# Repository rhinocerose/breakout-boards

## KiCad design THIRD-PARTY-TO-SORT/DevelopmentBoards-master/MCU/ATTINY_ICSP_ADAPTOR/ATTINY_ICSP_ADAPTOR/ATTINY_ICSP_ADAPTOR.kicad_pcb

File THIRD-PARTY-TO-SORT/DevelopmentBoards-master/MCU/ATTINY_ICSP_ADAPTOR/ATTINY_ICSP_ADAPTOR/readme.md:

<h2> ATTiny85 breadboard adaptor </h2>

<h3>Schematic</h3>

<h3>3D Renders</h3>

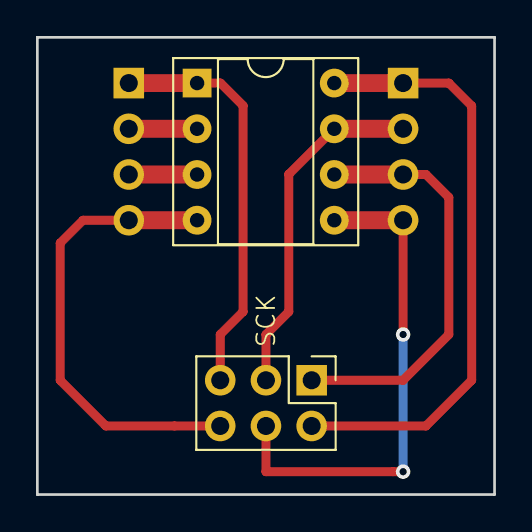
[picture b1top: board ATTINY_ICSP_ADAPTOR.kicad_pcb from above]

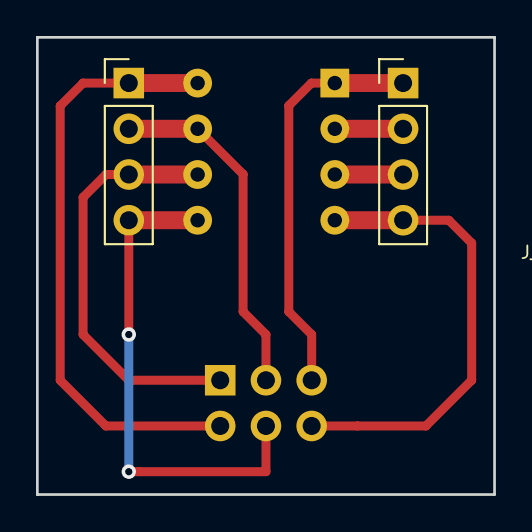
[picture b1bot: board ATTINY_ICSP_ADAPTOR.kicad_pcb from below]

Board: 2 copper layers, 25.4 x 25.4 mm, 4 parts (2 on the bottom side), 8 nets.

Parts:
J_ICSP1: AVR-ISP-6; PinHeader_2x03_P2.54mm_Vertical
J_PINS_1-4, J_PINS_5-8: Conn_01x04; PinHeader_1x04_P2.54mm_Vertical
U_MCU1: ATtiny85-20PU; DIP-8_W7.62mm_Socket

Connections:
unnamed: J_ICSP1.1, J_PINS_5-8.3, U_MCU1.6
unnamed: J_ICSP1.2, J_PINS_5-8.1, U_MCU1.8
unnamed: J_ICSP1.3, J_PINS_5-8.2, U_MCU1.7
unnamed: J_ICSP1.4, J_PINS_5-8.4, U_MCU1.5
unnamed: J_ICSP1.5, J_PINS_1-4.1, U_MCU1.1
unnamed: J_ICSP1.6, J_PINS_1-4.4, U_MCU1.4
unnamed: J_PINS_1-4.2, U_MCU1.2
unnamed: J_PINS_1-4.3, U_MCU1.3

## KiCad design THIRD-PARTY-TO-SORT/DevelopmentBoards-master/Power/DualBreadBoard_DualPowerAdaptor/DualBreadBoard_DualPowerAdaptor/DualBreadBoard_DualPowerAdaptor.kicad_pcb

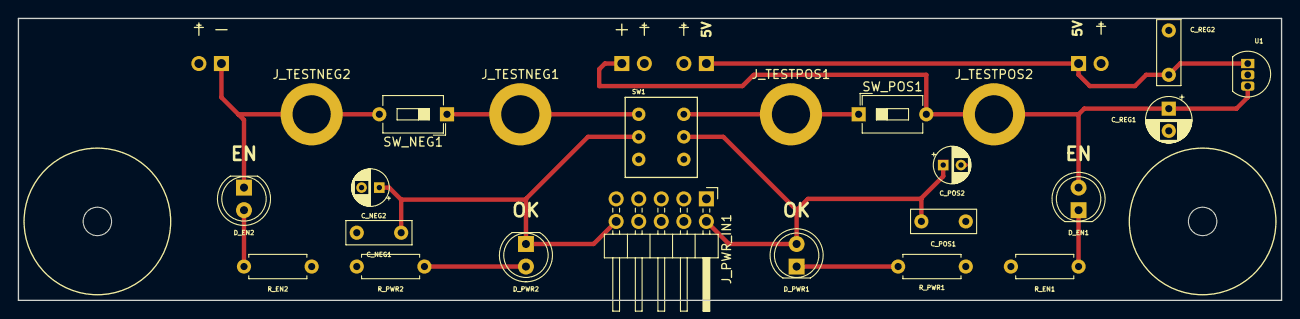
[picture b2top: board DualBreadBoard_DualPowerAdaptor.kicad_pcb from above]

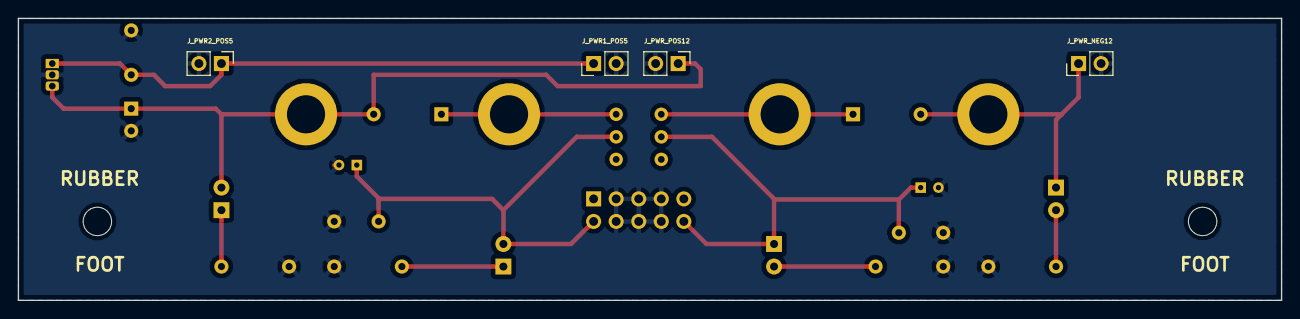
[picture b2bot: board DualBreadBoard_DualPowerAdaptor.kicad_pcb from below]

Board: 2 copper layers, 142.2 x 31.8 mm, 27 parts (4 on the bottom side), 12 nets.

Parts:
C_NEG1: 100nF; C_Rect_L7.2mm_W2.5mm_P5.00mm_FKS2_FKP2_MKS2_MKP2
C_NEG2: 10uF; CP_Radial_D4.0mm_P2.00mm
C_POS1: 100nF; C_Rect_L7.2mm_W2.5mm_P5.00mm_FKS2_FKP2_MKS2_MKP2
C_POS2: 10uF; CP_Radial_D4.0mm_P2.00mm
C_REG1: 330nF; CP_Radial_D5.0mm_P2.50mm
C_REG2: 100nF; C_Rect_L7.2mm_W2.5mm_P5.00mm_FKS2_FKP2_MKS2_MKP2
D_EN1, D_EN2: RED; LED_D5.0mm
D_PWR1, D_PWR2: RED; LED_D5.0mm
J_PWR1_POS5, J_PWR2_POS5: Conn_01x02; PinHeader_1x02_P2.54mm_Vertical
J_PWR_IN1: Conn_02x05_Odd_Even; PinHeader_2x05_P2.54mm_Horizontal
J_PWR_NEG12: Conn_01x02; PinHeader_1x02_P2.54mm_Vertical
J_PWR_POS12: Conn_01x02; PinHeader_1x02_P2.54mm_Vertical
J_TESTNEG1, J_TESTNEG2: Conn_01x01; MountingHole_4.3mm_M4_ISO14580_Pad
J_TESTPOS1, J_TESTPOS2: Conn_01x01; MountingHole_4.3mm_M4_ISO14580_Pad
R_EN1, R_EN2: 1K; R_Axial_DIN0207_L6.3mm_D2.5mm_P7.62mm_Horizontal
R_PWR1, R_PWR2: 1K; R_Axial_DIN0207_L6.3mm_D2.5mm_P7.62mm_Horizontal
SW1: SW_DPDT_x2; DPST_ToggleONOFF
SW_NEG1: SW_SPST; SW_DIP_SPSTx01_Slide_6.7x4.1mm_W7.62mm_P2.54mm_LowProfile
SW_POS1: SW_SPST; SW_DIP_SPSTx01_Slide_6.7x4.1mm_W7.62mm_P2.54mm_LowProfile
U1: LM78L05_TO92; TO-92L_Inline

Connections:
/5V: C_REG2.1, J_PWR1_POS5.1, J_PWR2_POS5.1, U1.1
/+12V: C_REG1.1, D_EN1.2, J_PWR_POS12.1, J_TESTPOS2.1, SW_POS1.2, U1.3
/-12V: D_EN2.1, J_PWR_NEG12.1, J_TESTNEG2.1, SW_NEG1.2
/GND: C_NEG1.1, C_NEG2.2, C_POS1.2, C_POS2.2, C_REG1.2, C_REG2.2, J_PWR1_POS5.2, J_PWR2_POS5.2, J_PWR_IN1.3, J_PWR_IN1.4, J_PWR_IN1.5, J_PWR_IN1.6, J_PWR_IN1.7, J_PWR_IN1.8, J_PWR_NEG12.2, J_PWR_POS12.2, R_EN1.1, R_EN2.1, R_PWR1.1, R_PWR2.1, U1.2
unnamed: C_NEG1.2, C_NEG2.1, D_PWR2.1, J_PWR_IN1.10, SW1.5
unnamed: C_POS1.1, C_POS2.1, D_PWR1.2, J_PWR_IN1.2, SW1.2
unnamed: D_EN1.1, R_EN1.2
unnamed: D_EN2.2, R_EN2.2
unnamed: D_PWR1.1, R_PWR1.2
unnamed: D_PWR2.2, R_PWR2.2
unnamed: J_TESTNEG1.1, SW1.4, SW_NEG1.1
unnamed: J_TESTPOS1.1, SW1.1, SW_POS1.1

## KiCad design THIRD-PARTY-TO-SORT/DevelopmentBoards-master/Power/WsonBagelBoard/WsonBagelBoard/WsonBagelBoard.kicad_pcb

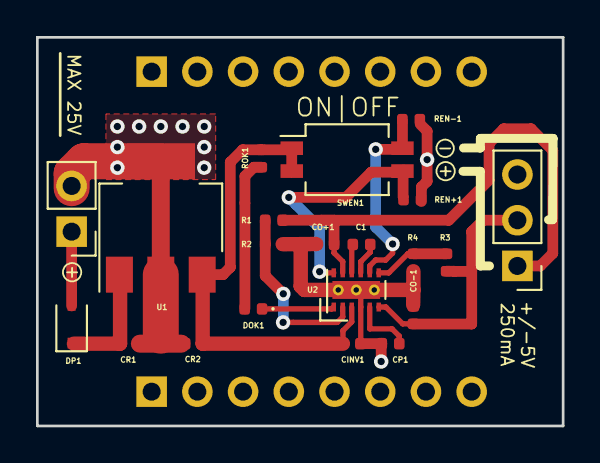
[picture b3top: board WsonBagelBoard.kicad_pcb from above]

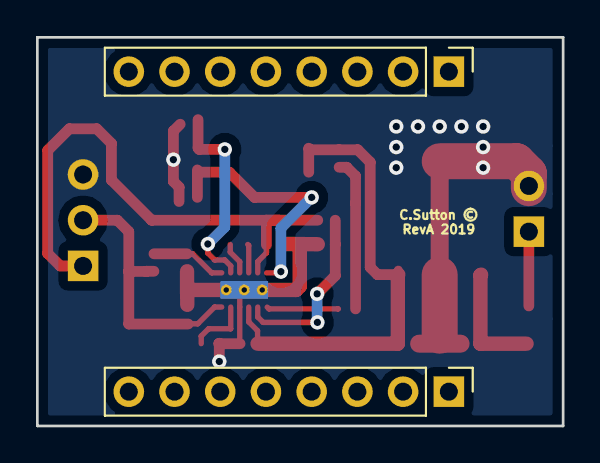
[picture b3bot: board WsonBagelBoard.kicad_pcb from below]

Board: 2 copper layers, 29.2 x 21.6 mm, 23 parts (2 on the bottom side), 15 nets.

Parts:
C1: 1u; C_0402_1005Metric
CINV1: 1u; C_0402_1005Metric
CO+1: 2.2u; C_0402_1005Metric
CO-1: 2.2u; C_0402_1005Metric
CP1: 4.7u; C_0402_1005Metric
CR1: C; C_0402_1005Metric
CR2: 100n; C_0402_1005Metric
DOK1: LED; LED_0402_1005Metric
DP1: D_Schottky; D_SOD-323
J_IN2: Conn_01x02; PinHeader_1x02_P2.54mm_Vertical
J_MNT1, J_MNT2: Conn_01x08; PinHeader_1x08_P2.54mm_Vertical
J_OUT1: Conn_01x03; PinHeader_1x03_P2.54mm_Vertical
R1, R3: 150K; R_0402_1005Metric
R2, R4: 50K; R_0402_1005Metric
REN+1: 10K; R_0402_1005Metric
REN-1: 10K; R_0402_1005Metric
ROK1: 10K; R_0402_1005Metric
SWEN1: SW_DIP_x02; SW_DIP_SPSTx02_Slide_Omron_A6H-2101_W6.15mm_P1.27mm
U1: uA7805; SOT-223-3_TabPin2
U2: LM27762; WSON-12-1EP_3x2mm_P0.5mm_EP1x2.65_ThermalVias

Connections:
/5VREG: CINV1.1, CR2.1, ROK1.2, SWEN1.1, SWEN1.2, U1.3, U2.3
/9VIN: CR1.1, DP1.1, U1.1
/EN+: REN+1.1, SWEN1.3, U2.12
/EN-: REN-1.1, SWEN1.4, U2.8
/GND: CINV1.2, CO+1.2, CO-1.2, CP1.2, CR1.2, CR2.2, J_IN2.2, J_OUT1.3, R2.1, R4.1, REN+1.2, REN-1.2, U1.2, U2.4, U2.13
/OUTREG+: CO+1.1, J_OUT1.1, R1.2, U2.11
/OUTREG-: CO-1.1, J_OUT1.2, R3.2, U2.6
/PGOOD: DOK1.1, U2.1
unnamed: C1.1, U2.9
unnamed: C1.2, U2.10
unnamed: CP1.1, U2.5
unnamed: DOK1.2, ROK1.1
unnamed: DP1.2, J_IN2.1
unnamed: R1.1, R2.2, U2.2
unnamed: R3.1, R4.2, U2.7

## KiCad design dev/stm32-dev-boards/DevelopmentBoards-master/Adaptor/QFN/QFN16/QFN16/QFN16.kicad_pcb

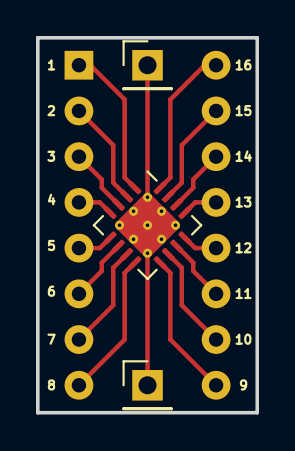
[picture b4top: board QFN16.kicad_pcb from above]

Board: 2 copper layers, 12.2 x 20.8 mm, 4 parts (0 on the bottom side), 17 nets.

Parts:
J_DIP16: Conn_01x16; DIP-16_W7.62mm_Socket
J_EP1, J_EP2: Conn_01x01; PinHeader_1x01_P2.54mm_Vertical
J_QFN16: Conn_01x17; QFN-16-1EP_4x4mm_P0.65mm_EP2.7x2.7mm_ThermalVias

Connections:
unnamed: J_DIP16.1, J_QFN16.1
unnamed: J_DIP16.2, J_QFN16.2
unnamed: J_DIP16.3, J_QFN16.3
unnamed: J_DIP16.4, J_QFN16.4
unnamed: J_DIP16.5, J_QFN16.5
unnamed: J_DIP16.6, J_QFN16.6
unnamed: J_DIP16.7, J_QFN16.7
unnamed: J_DIP16.8, J_QFN16.8
unnamed: J_DIP16.9, J_QFN16.9
unnamed: J_DIP16.10, J_QFN16.10
unnamed: J_DIP16.11, J_QFN16.11
unnamed: J_DIP16.12, J_QFN16.12
unnamed: J_DIP16.13, J_QFN16.13
unnamed: J_DIP16.14, J_QFN16.14
unnamed: J_DIP16.15, J_QFN16.15
unnamed: J_DIP16.16, J_QFN16.16
unnamed: J_EP1.1, J_EP2.1, J_QFN16.17

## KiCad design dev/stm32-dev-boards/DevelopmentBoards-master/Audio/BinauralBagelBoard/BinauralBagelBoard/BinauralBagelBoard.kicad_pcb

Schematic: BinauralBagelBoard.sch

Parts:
JIO1: Conn_02x02_Odd_Even; PinSocket_2x02_P2.54mm_Vertical
JMNT1, JMNT2: Conn_01x06; PinHeader_1x06_P2.54mm_Vertical
JOA1, JOA2: Conn_02x03_Odd_Even; PinSocket_2x03_P2.54mm_Vertical
JP_OA1, JP_OA2: Jumper; SolderJumper-2_P1.3mm_Open_TrianglePad1.0x1.5mm
J_INOUT1: JACK__MONO_2P_NC; JackSocket_Mono_PCB
J_PWRTHRU1, J_PWRTHRU2: Conn_01x03; PinHeader_1x03_P2.54mm_Horizontal
U_OA1: TL072; SOIC-8_3.9x4.9mm_P1.27mm

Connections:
/+5V: J_PWRTHRU1.3, J_PWRTHRU2.3, U_OA1.8 (V+)
/-5V: J_PWRTHRU1.2, J_PWRTHRU2.2, U_OA1.4 (V-)
/GND: JIO1.2, JIO1.4, J_INOUT1.2, J_INOUT1.3, J_INOUT1.4, J_PWRTHRU1.1, J_PWRTHRU2.1
/INOUT: JIO1.1, JIO1.3, J_INOUT1.1
/OAMA: JOA1.3, JOA1.4, JP_OA1.1, U_OA1.2 (-)
/OAMB: JOA2.3, JOA2.4, JP_OA2.1, U_OA1.6 (-)
/OAOA: JOA1.5, JOA1.6, JP_OA1.2, U_OA1.1
/OAOB: JOA2.5, JOA2.6, JP_OA2.2, U_OA1.7
/OAPA: JOA1.1, JOA1.2, U_OA1.3 (+)
/OAPB: JOA2.1, JOA2.2, U_OA1.5 (+)

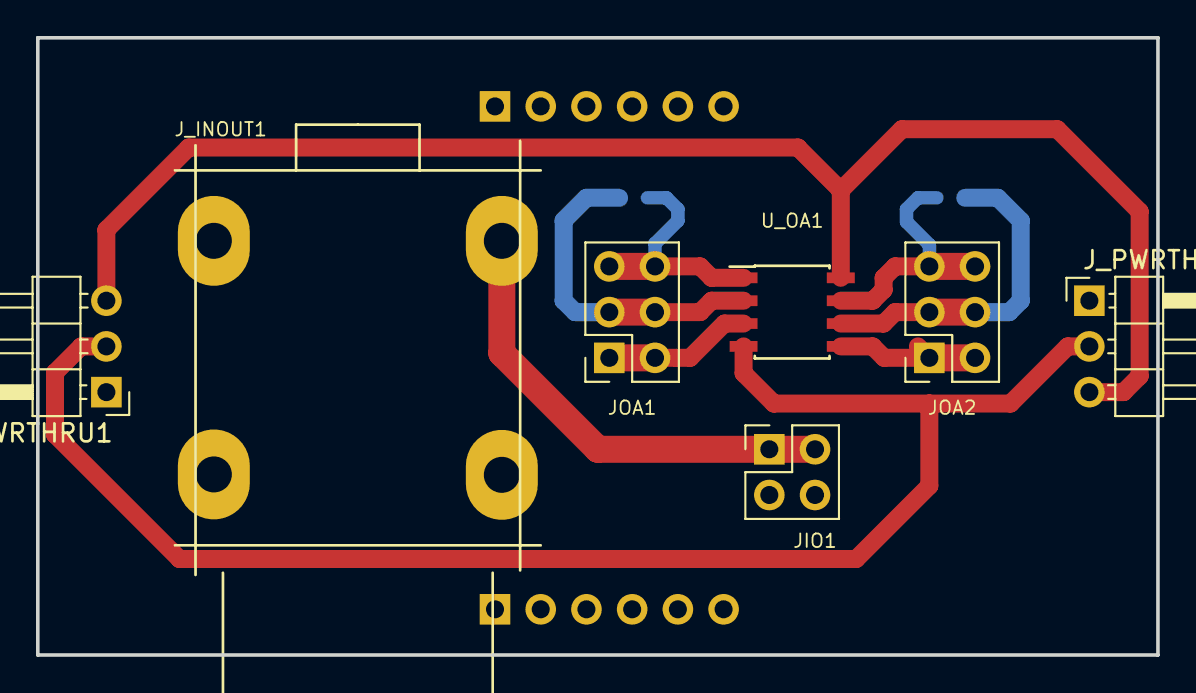
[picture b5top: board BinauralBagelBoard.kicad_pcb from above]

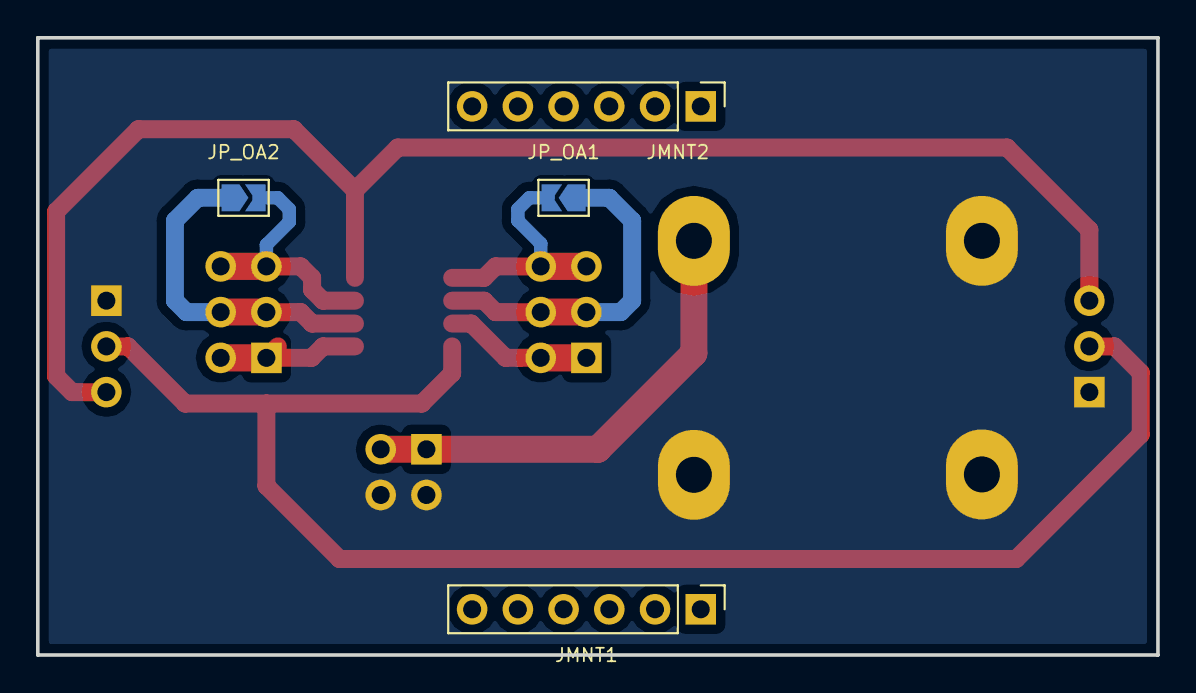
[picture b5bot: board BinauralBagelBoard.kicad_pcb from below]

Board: 2 copper layers, 62.2 x 34.3 mm, 11 parts (4 on the bottom side), 10 nets.

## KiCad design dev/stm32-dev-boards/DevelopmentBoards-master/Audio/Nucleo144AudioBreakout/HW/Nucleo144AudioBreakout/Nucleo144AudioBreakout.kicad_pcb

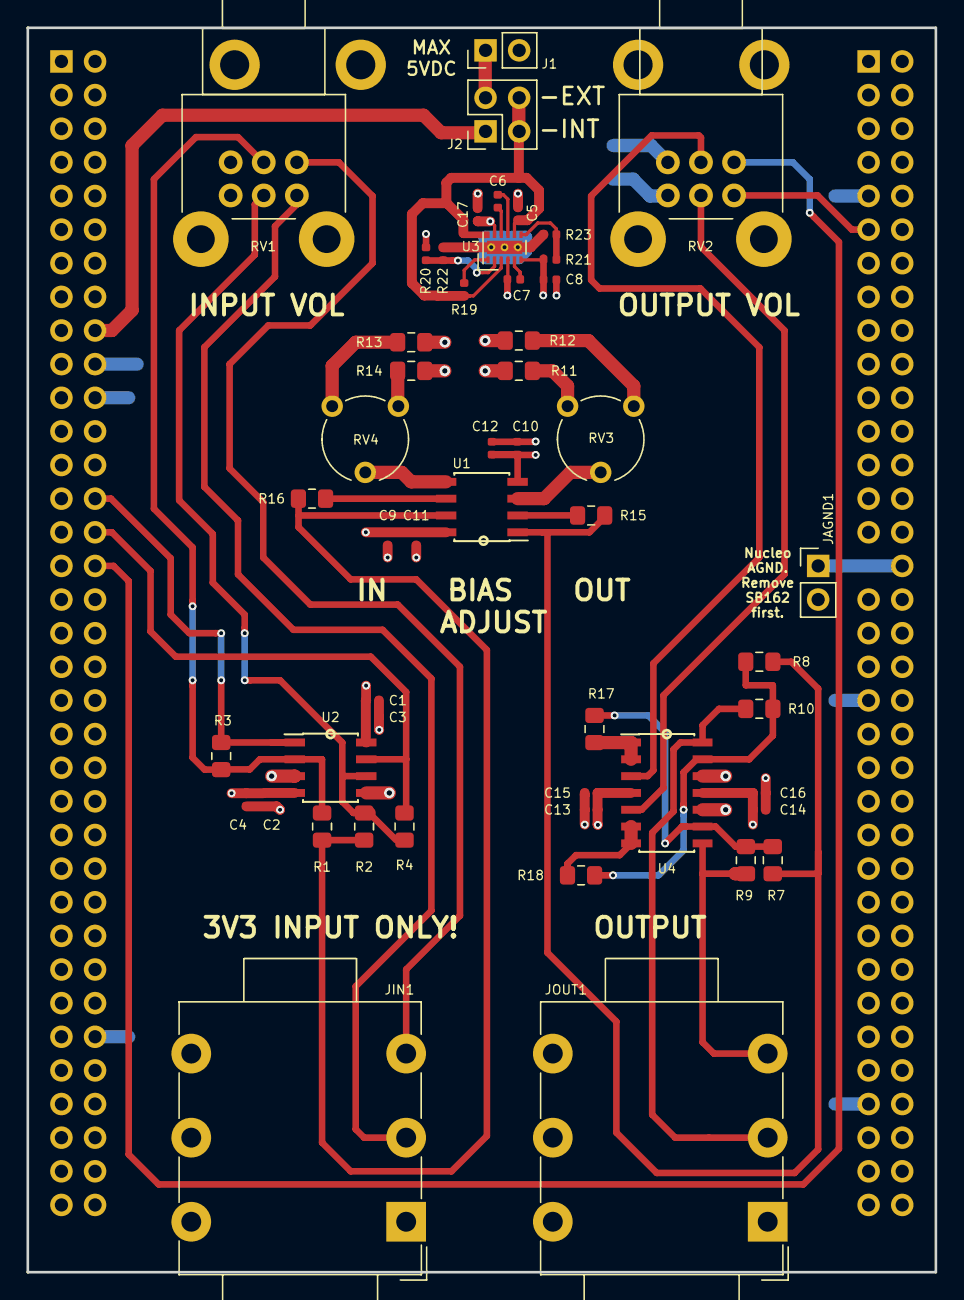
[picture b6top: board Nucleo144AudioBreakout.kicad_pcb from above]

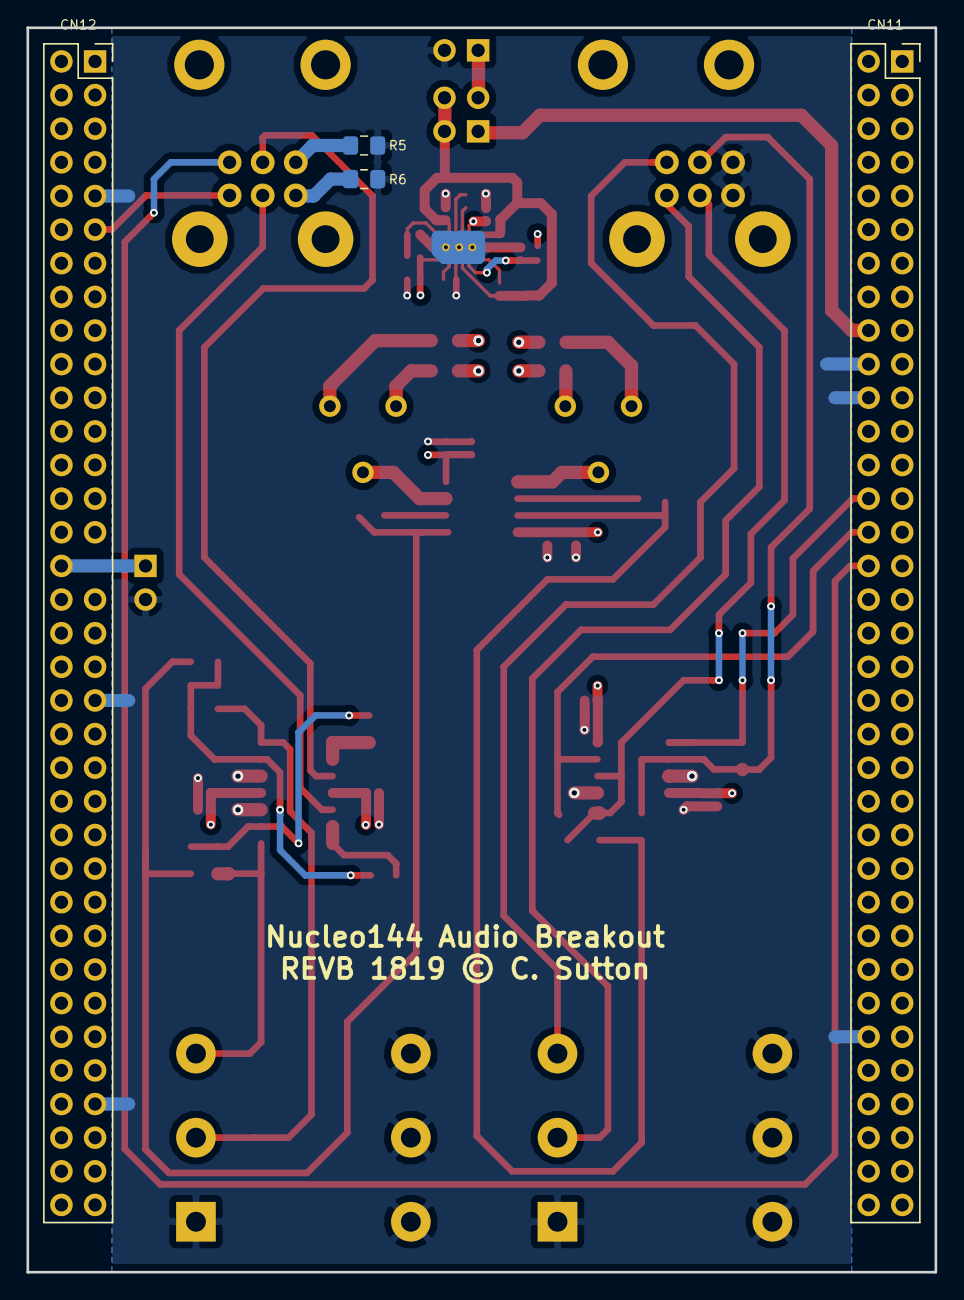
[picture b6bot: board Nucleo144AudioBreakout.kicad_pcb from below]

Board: 4 copper layers, 68.6 x 94.0 mm, 55 parts (4 on the bottom side), 41 nets.

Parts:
C1, C2, C9, C10, C13, C14: 100n; C_0402_1005Metric
C3, C4, C11, C12, C15, C16: 1u; C_0402_1005Metric
C5, C8, C17: 2.2u; C_0402_1005Metric
C6: 470n; C_0402_1005Metric
C7: 4.7u; C_0402_1005Metric
CN11, CN12: Nucleo144_Morpho; PinSocket_2x35_P2.54mm_Vertical
J1: Ext. Power; PinHeader_1x02_P2.54mm_Vertical
J2: Power Select; PinHeader_2x02_P2.54mm_Vertical
JAGND1: Conn_01x02; PinHeader_1x02_P2.54mm_Vertical
JIN1: Neutrik_NMJ6HFD2_TRS; Jack_3.5mm_Neutric_NMJ6HCD2_Horizontal
JOUT1: Neutrik_NMJ6HFD2_TRS; Jack_3.5mm_Neutric_NMJ6HCD2_Horizontal
R1, R2, R3, R4, R7, R8, R9, R10, R11, R12, R13, R14, R15, R16: 1K; R_0805_2012Metric_Pad1.15x1.40mm_HandSolder
R5, R6: 0R; R_0805_2012Metric_Pad1.15x1.40mm_HandSolder
R17, R18: 1k; R_0805_2012Metric_Pad1.15x1.40mm_HandSolder
R19: 10K; R_0402_1005Metric
R20, R21: 150K; R_0402_1005Metric
R22, R23: 50K; R_0402_1005Metric
RV1: 10K; Potentiometer_Alps_RK09L_Double_Horizontal
RV2: 100K; Potentiometer_Alps_RK09L_Double_Horizontal
RV3, RV4: 100K; Potentiometer_Piher_PT-6-V_Vertical
U1, U2: TL072; SOIC-8_3.9x4.9mm_P1.27mm
U3: LM27762; WSON-12-1EP_3x2mm_P0.5mm_EP1x2.65_ThermalVias
U4: TL074; SOIC-14_3.9x8.7mm_P1.27mm

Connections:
+5V: C1.1, C3.1, C9.1, C11.1, C13.1, C15.1, C17.1, R11.1, R13.1, R20.2, U1.8, U2.8, U3.11, U4.4
-5V: C2.1, C4.1, C8.1, C10.1, C12.1, C14.1, C16.1, R12.2, R14.2, R21.1, U1.4, U2.4, U3.6, U4.11
/FLAT_LINE_ADJUST_IN: R1.2, R2.2, R16.1, U1.7
/FLAT_LINE_ADJUST_OUT: R7.2, R8.2, R15.1, U1.1
/LM27762PSU/5V: C5.1, J2.3, J2.4, R19.2, U3.3, U3.8, U3.12
/LM27762PSU/VDDEXT: J1.1, J2.2
/PA0_ADC1_IN1: CN11.28, R3.1, U2.1
/PA1_ADC1_IN2: CN11.30, R4.1, U2.7
/PA4_DAC_OUT1: CN11.32, RV2.1
/PA5_DAC_OUT2: CN12.11, RV2.4
GNDS: C1.2, C2.2, C3.2, C4.2, C5.2, C7.1, C8.2, C9.2, C10.2, C11.2, C12.2, C13.2, C14.2, C15.2, C16.2, C17.2, CN11.20, CN11.22, CN11.60, CN12.9, CN12.39, CN12.63, J1.2, JAGND1.2, JIN1.1, JIN1.4, JIN1.5, JIN1.6, JOUT1.1, JOUT1.4, JOUT1.5, JOUT1.6, R5.1, R6.1, R22.1, R23.2, RV1.3, RV1.6, U2.3, U2.5, U3.4, U3.13, U4.10, U4.12
unnamed: C6.1, U3.9
unnamed: C6.2, U3.10
unnamed: C7.2, U3.5
unnamed: CN12.32, JAGND1.1
unnamed: JIN1.2, RV1.1
unnamed: JIN1.3, RV1.4
unnamed: JOUT1.2, R9.1, U4.8
unnamed: JOUT1.3, R10.1, U4.14
unnamed: R1.1, R3.2, RV1.2, U2.2
unnamed: R2.1, R4.2, RV1.5, U2.6
unnamed: R5.2, RV2.3
unnamed: R6.2, RV2.6
unnamed: R8.1, R10.2, R18.2, U4.13
unnamed: R11.2, RV3.1
unnamed: R12.1, RV3.3
unnamed: R13.2, RV4.1
unnamed: R14.1, RV4.3
unnamed: R15.2, U1.2
unnamed: R16.2, U1.6
unnamed: R17.1, U4.1, U4.2
unnamed: R7.1, R9.2, R17.2, U4.9
unnamed: R18.1, U4.6, U4.7
unnamed: R19.1, U3.1
unnamed: R20.1, R22.2, U3.2
unnamed: R21.2, R23.1, U3.7
unnamed: RV2.2, U4.3
unnamed: RV2.5, U4.5
unnamed: RV3.2, U1.3
unnamed: RV4.2, U1.5
VDD: CN11.18, J2.1

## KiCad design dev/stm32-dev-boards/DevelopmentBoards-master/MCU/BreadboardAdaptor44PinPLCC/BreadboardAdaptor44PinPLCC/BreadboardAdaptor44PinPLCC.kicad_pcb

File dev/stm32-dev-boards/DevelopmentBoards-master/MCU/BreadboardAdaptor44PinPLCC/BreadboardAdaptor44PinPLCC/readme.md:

<h2> 44Pin PLCC breadboard adaptor </h2>

<h3>Schematic</h3>

<h3> Board Layout</h3>

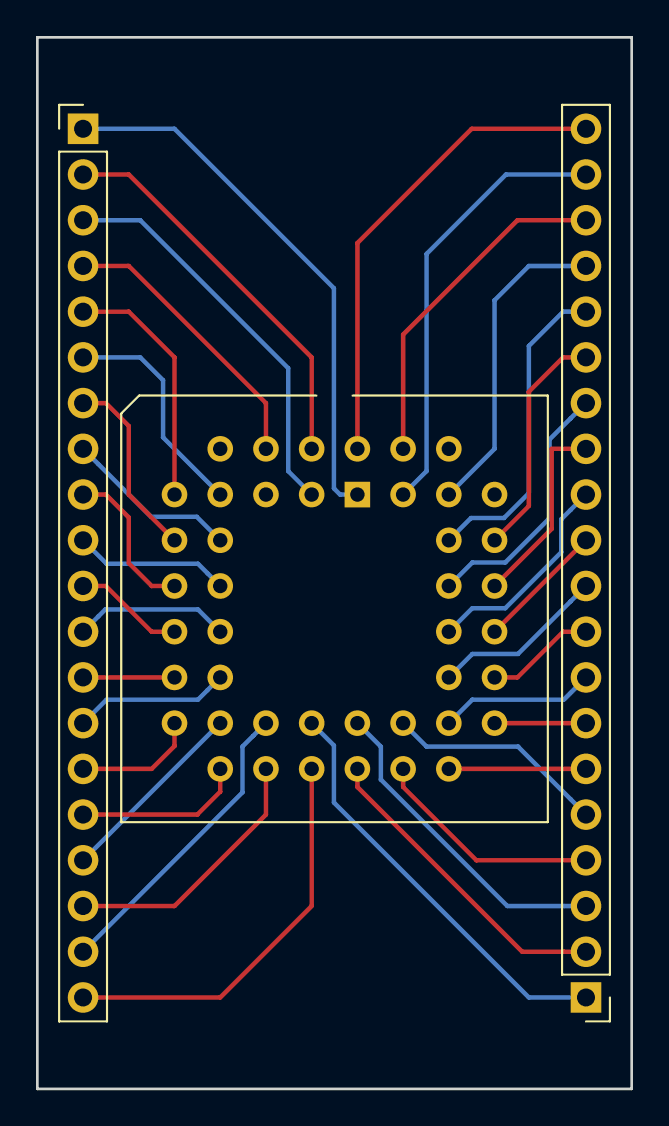
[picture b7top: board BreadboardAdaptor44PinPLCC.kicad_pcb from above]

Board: 2 copper layers, 33.0 x 58.4 mm, 3 parts (0 on the bottom side), 40 nets.

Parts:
J_1_22_PDIP1, J_23_44_PDIP2: Conn_01x20; PinHeader_1x20_P2.54mm_Vertical
U_PLCC1: 44PinPLCCSocket; PLCC-44_THT-Socket

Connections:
unnamed: J_1_22_PDIP1.1, U_PLCC1.1
unnamed: J_1_22_PDIP1.2, U_PLCC1.2
unnamed: J_1_22_PDIP1.3, U_PLCC1.3
unnamed: J_1_22_PDIP1.4, U_PLCC1.4
unnamed: J_1_22_PDIP1.5, U_PLCC1.7
unnamed: J_1_22_PDIP1.6, U_PLCC1.8
unnamed: J_1_22_PDIP1.7, U_PLCC1.9
unnamed: J_1_22_PDIP1.8, U_PLCC1.10
unnamed: J_1_22_PDIP1.9, U_PLCC1.11
unnamed: J_1_22_PDIP1.10, U_PLCC1.12
unnamed: J_1_22_PDIP1.11, U_PLCC1.13
unnamed: J_1_22_PDIP1.12, U_PLCC1.14
unnamed: J_1_22_PDIP1.13, U_PLCC1.15
unnamed: J_1_22_PDIP1.14, U_PLCC1.16
unnamed: J_1_22_PDIP1.15, U_PLCC1.17
unnamed: J_1_22_PDIP1.16, U_PLCC1.18
unnamed: J_1_22_PDIP1.17, U_PLCC1.19
unnamed: J_1_22_PDIP1.18, U_PLCC1.20
unnamed: J_1_22_PDIP1.19, U_PLCC1.21
unnamed: J_1_22_PDIP1.20, U_PLCC1.22
unnamed: J_23_44_PDIP2.1, U_PLCC1.23
unnamed: J_23_44_PDIP2.2, U_PLCC1.24
unnamed: J_23_44_PDIP2.3, U_PLCC1.25
unnamed: J_23_44_PDIP2.4, U_PLCC1.26
unnamed: J_23_44_PDIP2.5, U_PLCC1.27
unnamed: J_23_44_PDIP2.6, U_PLCC1.28
unnamed: J_23_44_PDIP2.7, U_PLCC1.29
unnamed: J_23_44_PDIP2.8, U_PLCC1.30
unnamed: J_23_44_PDIP2.9, U_PLCC1.31
unnamed: J_23_44_PDIP2.10, U_PLCC1.32
unnamed: J_23_44_PDIP2.11, U_PLCC1.33
unnamed: J_23_44_PDIP2.12, U_PLCC1.34
unnamed: J_23_44_PDIP2.13, U_PLCC1.35
unnamed: J_23_44_PDIP2.14, U_PLCC1.36
unnamed: J_23_44_PDIP2.15, U_PLCC1.37
unnamed: J_23_44_PDIP2.16, U_PLCC1.38
unnamed: J_23_44_PDIP2.17, U_PLCC1.41
unnamed: J_23_44_PDIP2.18, U_PLCC1.42
unnamed: J_23_44_PDIP2.19, U_PLCC1.43
unnamed: J_23_44_PDIP2.20, U_PLCC1.44

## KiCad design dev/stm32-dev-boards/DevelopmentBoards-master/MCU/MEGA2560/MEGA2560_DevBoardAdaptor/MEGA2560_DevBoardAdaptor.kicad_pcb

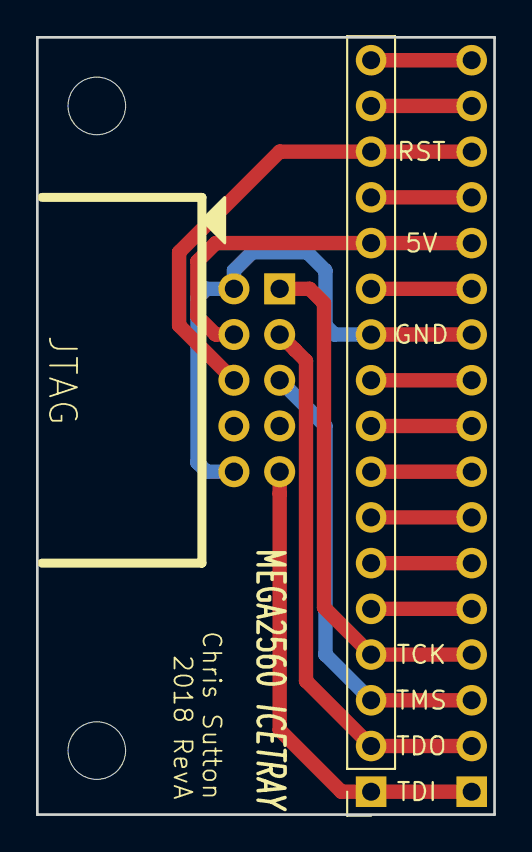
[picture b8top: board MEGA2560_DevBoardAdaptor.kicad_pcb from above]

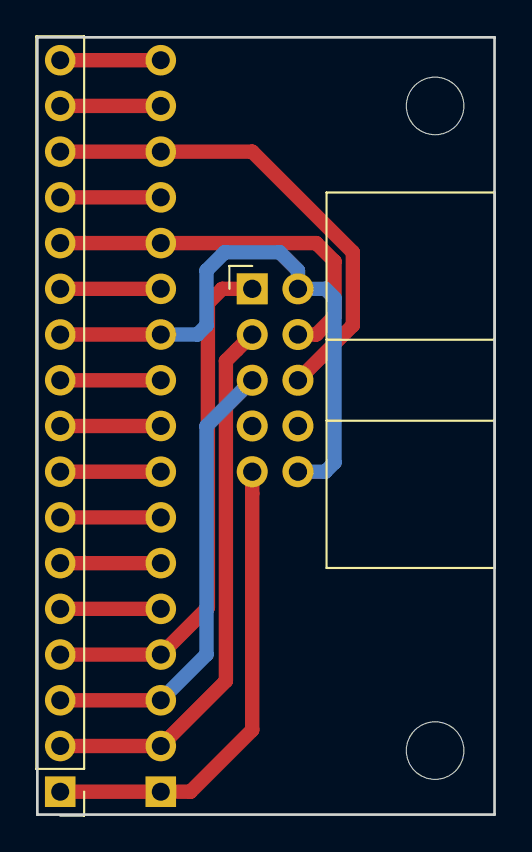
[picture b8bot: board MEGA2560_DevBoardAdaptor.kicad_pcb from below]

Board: 2 copper layers, 25.4 x 43.2 mm, 3 parts (2 on the bottom side), 16 nets.

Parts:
J_AUX1: Conn_01x17; PinSocket_1x17_P2.54mm_Vertical
J_BRD1: Conn_01x17; PinHeader_1x17_P2.54mm_Vertical
J_JTAG1: Conn_02x05_Odd_Even; IDC-Header_2x05_P2.54mm_Horizontal

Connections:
/5V: J_AUX1.13, J_BRD1.13, J_JTAG1.4
/A4_TCK_1: J_AUX1.4, J_BRD1.4, J_JTAG1.1
/A5_TMS_5: J_AUX1.3, J_BRD1.3, J_JTAG1.5
/A6_TDO_3: J_AUX1.2, J_BRD1.2, J_JTAG1.3
/A7_TDI_9: J_AUX1.1, J_BRD1.1, J_JTAG1.9
/GND: J_AUX1.11, J_BRD1.11, J_JTAG1.2, J_JTAG1.10
/RESET: J_AUX1.15, J_BRD1.15, J_JTAG1.6
unnamed: J_AUX1.5, J_BRD1.5
unnamed: J_AUX1.6, J_BRD1.6
unnamed: J_AUX1.7, J_BRD1.7
unnamed: J_AUX1.8, J_BRD1.8
unnamed: J_AUX1.10, J_BRD1.10
unnamed: J_AUX1.12, J_BRD1.12
unnamed: J_AUX1.14, J_BRD1.14
unnamed: J_AUX1.16, J_BRD1.16
unnamed: J_AUX1.17, J_BRD1.17

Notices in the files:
dev/stm32-dev-boards/DevelopmentBoards-master/Audio/Nucleo144AudioBreakout/HW/Nucleo144AudioBreakout/Nucleo144AudioBreakout.kicad_pcb:
REVB 1819 © C. Sutton
